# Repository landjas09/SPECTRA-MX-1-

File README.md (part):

# SPECTRA MX-1

*STM32-controlled mixed-signal acquisition and generation board*

SPECTRA MX-1 is a four-layer PCB designed in KiCad for low-frequency analog acquisition and signal generation, with a target operating band of **20 Hz–20 kHz**. An STM32F103 controls an external differential-input ADC and a dual-channel DAC through separate SPI interfaces. The board combines input conditioning, active filtering, reference generation, USB-C connectivity and BNC analog connectors.

**Revision:** A · **Author:** [Akram Landjas](https://github.com/landjas09) ·

*Studio visualization of the Rev A assembly.*

## Contents

- [Project status](#project-status)
- [Hardware specification](#hardware-specification)
- [System architecture](#system-architecture)
- [Analog acquisition path](#analog-acquisition-path)
- [Analog generation path](#analog-generation-path)
- [Nominal filter analysis](#nominal-filter-analysis)
- [Power architecture](#power-architecture)
- [MCU, clocks and pin assignments](#mcu-clocks-and-pin-assignments)
- [External interfaces](#external-interfaces)
- [PCB stackup and mechanics](#pcb-stackup-and-mechanics)
- [BOM and component selection](#bom-and-component-selection)
- [Firmware scope](#firmware-scope)
- [Bring-up and validation](#bring-up-and-validation)
- [Pre-release engineering review](#pre-release-engineering-review)
- [3D models, renders and animation](#3d-models-renders-and-animation)
- [Development roadmap](#development-roadmap)
- [Contributing and technical feedback](#contributing-and-technical-feedback)
- [References](#references)
- [Acknowledgments and licensing](#acknowledgments-and-licensing)

## Project status

This documentation describes the supplied **Rev A PCB snapshot**, saved by KiCad 10.0. Connections, values, component references and stackup data were extracted from MixedSignal_Analyzer_Generator.kicad_pcb. Device characteristics are identified separately from calculated circuit estimates and board measurements.

| Item | Current status |
| --- | --- |
| PCB layout and embedded footprints | Available in the supplied PCB snapshot |
| Board/component 3D export | Available as SPECTRA_MX1.glb |
| Studio renders and animation | Available |
| Main project file, root schematic and child sheets | Included in the repository |
| Custom library sources and library tables | Required for a complete editable project release |
| BOM / purchasing data | Draft; imported metadata and generic components require review |
| Firmware and host software | Not included in the reviewed handoff |
| ERC, DRC and fabrication-release reports | Results not supplied |
| Fabrication, assembly and electrical validation | Pending |
| Measured bandwidth, noise, distortion, ENOB and throughput | Pending |

The 20 Hz–20 kHz band is a **design target**. Converter bit depths are device specifications. The filter plots below are **analytical estimates using the current component values**. A validated input range, output load rating and sustained streaming rate have not yet been established.

## Hardware specification

| Parameter | Rev A implementation / interpretation |
| --- | --- |
| MCU | U200: STM32F103CBTx; manufacturer-part field identifies STM32F103CBT6 |
| MCU resources | Arm Cortex-M3; 128 KB Flash, 20 KB SRAM; device supports a CPU clock up to 72 MHz |
| External clock | Y200: 16 MHz crystal; C208/C209: 10 pF; R201: 0 Ω series link |
| External ADC | U302: ADC141S626CIMM/NOPB; 14-bit SAR, differential input, external reference |
| ADC bus | SPI1; chip select, clock and data-out routed; MCU MOSI not used for this ADC |
| ADC device conversion-rate range | Manufacturer specifies 50–250 kSPS; timing/performance conditions must be checked for the board's nominal 3.3 V supplies |
| ADC voltage reference | U303: REF3033; nominal 3.3 V |
| DAC | U400: DAC7563SDGSR; two 12-bit buffered voltage-output channels |
| DAC bus / controls | SPI2; independent active-low SYNC, LDAC and CLR control |
| Externally routed DAC output | Channel A through the reconstruction filter to J400 |
| DAC channel B | Connected to R402, a 10 kΩ load to GND; no second analog-output connector |
| Op amps | Four MCP6001U devices: U102, U300, U301 and U401 |
| Analog input | J300: single-ended BNC; AC-coupled conditioning and biased converter drive |
| Analog output | J400: BNC; DC-coupled filtered voltage output with 49.9 Ω series resistor |
| Host interface | J201: USB-C receptacle carrying USB 2.0 D+/D− and 5 V VBUS; MCU supports USB full speed |
| Debug | J200: 2 × 5, 1.27 mm header carrying SWD, SWO, reset, GND and 3.3 V reference |
| Primary supply | USB-C VBUS, nominal 5 V |
| Power domains | +5V, +3.3V, +3.3VA, MCU VDDA, buffered VCOM and ADC reference |
| PCB | Four copper layers; current internal zones connect both In1.Cu and In2.Cu to GND |
| Board outline | Approximately 60 × 75 mm, excluding protruding connector bodies |
| Mounting | Four 3.2 mm non-plated M3 mounting holes |
| Modeled finish / thickness | ENIG; approximately 1.57 mm copper/dielectric stack, approximately 1.60 mm including modeled solder mask |
| Design tool | PCB file identifies KiCad 10.0 |

Device limits and specifications above do not establish equivalent board-level performance. See the [manufacturer references](#references) and [validation plan](#bring-up-and-validation).

## System architecture

```mermaid
flowchart TD
    IN["J300: BNC input"] --> FRONT["Protection, coupling and U300 buffer"]
    FRONT --> AAF["Three-pole filter: U301"]
    AAF --> ADC["U302: 14-bit ADC"]
    ADC --> MCU["U200: STM32F103"]
    USB["J201: USB-C host interface"] <--> MCU
    DEBUG["J200: SWD / SWO / reset"] --> MCU
    MCU --> DAC["U400: 12-bit DAC, channel A"]
    DAC --> RECON["Three-pole filter: U401"]
    RECON --> OUT["J400: BNC output"]
```

The input and output processing chains are physically grouped near the BNC connectors. The digital-control and USB circuitry occupy the upper part of the PCB. Separate SPI peripherals allow acquisition and generation to be scheduled independently.

**Rev A bias generation is fixed:** VCOM is produced by a resistor divider and an op-amp buffer. DAC channel B is not connected to the bias generator in this snapshot.

## Analog acquisition path

### Input connector and protection

J300's center contact connects to /ADC/IN; its shield contacts connect to GND. D300, labeled CDSOD323-T03C, is placed between the input net and GND.

R300 = 1 kΩ and C300 = 150 pF form the first input RF-filtering network. R301 = 2.2 MΩ provides a return path from /ADC/IN_RF to GND.

Ignoring the following coupling/bias network and source impedance, the simple R300/C300 pole is approximately **1.06 MHz**. Its role is upstream high-frequency filtering; the following active filter sets the useful low-frequency response.

### AC coupling, bias and first buffer

C301 = 100 nF connects /ADC/IN_RF to /ADC/IN_BUFF. R302 = 2.2 MΩ biases /ADC/IN_BUFF to VCOM. U300 is an MCP6001U configured as a unity-gain buffer.

For a low-impedance source, the dominant coupling estimate is:

$$
f_{\mathrm{HP}} \approx \frac{1}{2\pi R_{302}C_{301}} \approx 0.72\ \mathrm{Hz}.
$$

This estimate depends on the source and the other return paths. **20 Hz is the lower edge of the stated target band, not the calculated −3 dB frequency of C301/R302.** The high-value bias resistance also makes leakage, contamination and startup settling relevant during assembly and validation.

### Active anti-alias filter

The signal at /ADC/IN_BUFF_OUT passes through a three-pole unity-gain RC/active network using U301. The topology combines the initial RC section with a buffered Sallen–Key section.

| Function | Components |
| --- | --- |
| First series resistor / shunt capacitor | R303 = 6.8 kΩ; C303 = 1 nF |
| Following series resistors | R304 = 22 kΩ; R305 = 12 kΩ |
| Feedback capacitor to the buffer output | C305 = 1 nF |
| Final input shunt capacitor | C304 = 150 pF |
| Unity-gain buffer | U301, MCP6001U |

The resulting nominal response is discussed in [Nominal filter analysis](#nominal-filter-analysis). Actual response depends on op-amp behavior, component tolerances and loading.

### Converter input network

U301 drives /ADC/ADC_IN+ through R306 = 1 kΩ. The ADC negative input is biased from VCOM through R307 = 1 kΩ. C307 = 150 pF connects the two ADC input nets.

This produces a nominal differential RC pole around **531 kHz** when approximated using R306 + R307. The actual SAR sampling network adds switched-capacitor loading, so acquisition settling must also be checked.

The external BNC signal is single-ended. The ADC measures the conditioned positive input relative to the biased negative input.

### ADC reference and supplies

- U302 VA, pin 10, connects to +3.3VA.
- U302 VIO, pin 9, connects to +3.3V.
- U303 REF3033 receives +5V through R308 = 49.9 Ω.
- C309 = 10 µF filters /ADC/ADC_VREF_VIN.
- U303's output connects to /ADC/ADC_Vref and U302 pin 1.
- C310 = 10 µF and C311 = 100 nF decouple the ADC reference.

The ideal R308/C309 supply-filter pole is approximately **319 Hz**. It is an input-supply filter for the reference, not a series filter between the reference output and ADC pin.

### Code interpretation and input range

The ADC's serial result is a **14-bit signed two's-complement value**. After extracting and sign-extending the conversion bits correctly, its ideal differential-voltage relationship is:

$$
V_{\mathrm{IN+}}-V_{\mathrm{IN-}}
\approx D_{\mathrm{signed}}\frac{2V_{\mathrm{REF}}}{2^{14}}.
$$

At nominal VREF = 3.3 V, the ideal differential code step is approximately **0.403 mV**.

The selected reference and input topology require engineering review. TI's full-range single-ended guidance uses VREF no greater than VA/2. Rev A selects a nominal 3.3 V reference while driving the ADC from a nominal 3.3 V analog supply and holding the negative input near 1.65 V. Reference tolerance, valid common-mode range, available signal swing and code utilization must therefore be resolved before publishing an external-input amplitude rating.

## Analog generation path

### DAC and digital control

U400 is a DAC7563 dual-channel, 12-bit voltage-output DAC. SPI2 carries commands to its DIN pin, with separate GPIO control for SYNC, LDAC and CLR.

The DAC accepts a **24-bit serial command frame**. Firmware must follow the command/address/data arrangement and timing in the DAC7563 datasheet; the register width is distinct from its 12-bit conversion resolution.

In Rev A:

- Channel A, /DAC/DAC_OUT_A, drives the output-filter chain.
- Channel B, /DAC/DAC_OUT_B, is connected to R402 = 10 kΩ to GND.
- AVDD connects to +3.3V.
- C400 = 10 µF and C401 = 100 nF decouple the supply.
- C402 = 1 µF connects the reference pin to GND.

### Reference and gain configuration

The internal 2.5 V reference is available by command and is disabled at power-up. Enabling it selects a gain configuration that must be handled explicitly.

For this nominal 3.3 V supply, **gain = 1 with the internal 2.5 V reference is the proposed initial configuration**. A 5 V full-scale request from gain = 2 exceeds the supply headroom. This is a firmware requirement to validate, not an implemented configuration reported by this repository.

For gain = 1:

$$
V_{\mathrm{DAC,A}} \approx 2.5\ \mathrm{V}\frac{D}{4096},
\qquad 0\le D\le4095.
$$

The ideal code step is approximately 0.610 mV. Codes 0, 2048 and 4095 nominally request 0 V, 1.25 V and 2.4994 V before output errors and loading. These are calculation values for bring-up, not measured output specifications.

### Reconstruction filter and BNC output

| Function | Components |
| --- | --- |
| First series resistor / shunt capacitor | R401 = 6.8 kΩ; C403 = 1 nF |
| Following series resistors | R403 = 22 kΩ; R404 = 12 kΩ |
| Feedback capacitor to the buffer output | C406 = 1 nF |
| Final input shunt capacitor | C404 = 150 pF |
| Unity-gain output buffer | U401, MCP6001U |
| BNC series resistor | R405 = 49.9 Ω |
| Output protection device | D400, CDSOD323-T03C |

The filter values match the ADC anti-alias network. U401's output drives J400 through R405. There is **no series output AC-coupling capacitor** in the reviewed path, so the output carries its DC level as well as the generated waveform.

R405 contributes approximately 50 Ω of series resistance. A 50 Ω BNC connector designation does not establish a validated 50 Ω load-drive capability. Initial characterization should use a high-impedance measurement input; output-current capability, loaded swing and cable-capacitance stability remain to be measured.

## Nominal filter analysis

Both active low-pass stages use the same resistor/capacitor values. A small-signal model with an ideal unity-gain buffer gives:

$$
H_{\mathrm{LP}}(s)=
\frac{1}{
1+(12.92\times10^{-6})s+
(8.652\times10^{-11})s^2+
(2.6928\times10^{-16})s^3
},
\qquad s=j2\pi f.
$$

| Frequency / metric | Ideal response of one low-pass stage |
| --- | --- |
| DC gain | 1 V/V |
| 1 kHz | Approximately +0.001 dB |
| 10 kHz | Approximately +0.050 dB |
| 20 kHz | Approximately −1.21 dB |
| −3 dB frequency | Approximately 24.05 kHz |
| 40 kHz | Approximately −13.22 dB |
| 50 kHz | Approximately −18.76 dB |
| 100 kHz | Approximately −36.57 dB |
| High-frequency asymptotic slope | −60 dB/decade |

**Model scope:** this is the common three-pole low-pass network only. It excludes finite op-amp gain/bandwidth, ADC sampling kickback, reference noise, source/load impedance, component tolerances, coupling/protection networks and PCB parasitics. End-to-end DAC-to-ADC loopback passes through both low-pass stages.

The [analysis script](docs/analysis/nominal_filter.py) and [numerical results](docs/analysis/nominal_filter_results.json) accompany this README.

To regenerate the analytical figure and results:

```bash
python -m pip install numpy scipy matplotlib
python docs/analysis/nominal_filter.py
```

For a 20 kHz signal band, the sample rate must exceed 40 kSPS and provide practical anti-aliasing margin. The existing filter's attenuation at the chosen Nyquist frequency must be evaluated against the required alias rejection. No ADC sample rate, DAC update rate or spectral-performance result is claimed as firmware-validated yet.

## Power architecture

```mermaid
flowchart TD
    VBUS["USB-C VBUS: nominal 5 V"] --> ENTRY["L100 and entry capacitors"]
    ENTRY --> FIVE["+5V"]
    FIVE --> BUCK["U100: buck to +3.3V"]
    BUCK --> DIGITAL["MCU, DAC and ADC digital supply"]
    FIVE --> AIN["R100 / C102 input filter"]
    AIN --> LDO["U101: +3.3VA analog rail"]
    LDO --> ANALOG["Op amps and ADC analog supply"]
    LDO --> BIAS["Divider and U102: VCOM"]
    FIVE --> RIN["R308 / C309 input filter"]
    RIN --> REF["U303: ADC reference"]
```

### USB entry and digital rail

L100 is labeled **100 nH** in the inductor symbol. C101 = 1 µF is connected from VBUS to GND, and C100 = 1 µF is connected from +5V to GND.

U100 TLV62569DBVR generates the digital rail. Its enable and input pins connect to +5V. L101 is labeled MWSA0603S-150MT; imported component metadata identifies 15 µH. C104 and C105 are 22 µF input/output capacitors.

With R101 = 100 kΩ, R102 = 22 kΩ and the regulator's nominal 0.6 V feedback reference:

$$
V_{\mathrm{OUT,ideal}}\approx0.6(1+100/22)\approx3.327\ \mathrm{V}.
$$

The rail is named +3.3V. Its assembled regulation, ripple, startup and load response must be measured. C106 is a feed-forward capacitor footprint labeled DNP.

The regulator's component rating does not establish a 2 A USB-powered board rating. Available current depends on the USB source, entry network, inductor, thermal behavior and the final power budget.

### Analog supply

R100 = 10 Ω and C102 = 22 µF filter the +5V supply before U101, labeled HT7533-1. U101's output is +3.3VA, with C103 = 22 µF on that rail.

The ideal input RC pole is approximately **723 Hz**. R100 also creates a load-dependent DC drop, so LDO dropout and analog current must be checked together.

The imported U101 manufacturer field identifies UMW. Confirm the exact supplier part, current rating, pinout and stability requirements when completing the BOM rather than assuming every similarly named regulator has identical specifications.

### VCOM generation

R105 = 1 kΩ to +3.3VA and R104 = 1 kΩ to GND form a nominal half-supply divider. C107 = 22 µF filters the divider node, /Power/VREF. U102 MCP6001U buffers it as VCOM.

VCOM is nominally **1.65 V** when +3.3VA is 3.3 V. The divider's 500 Ω Thevenin resistance and C107 give an ideal pole near **14.5 Hz**. The buffer supplies the bias node without asking the divider to drive the ADC input network directly.

### MCU analog supply

L201 = 10 nH connects +3.3V to the MCU's VDDA net. C205 = 10 nF and C206 = 1 µF decouple VDDA; U200 VSSA connects to GND.

**VDDA and +3.3VA are distinct nets:** VDDA supplies the MCU's analog domain, while +3.3VA supplies the external analog circuitry and ADC VA.

| Net | Source / nominal value | Main loads |
| --- | --- | --- |
| VBUS | USB-C, nominal 5 V | Entry filter and USB protection reference |
| +5V | VBUS after L100 | Buck, analog-supply filter and ADC-reference supply filter |
| +3.3V | U100 buck, nominal 3.3 V | MCU VDD/VBAT, DAC AVDD, ADC VIO, LED and debug reference |
| +3.3VA | U101 linear regulator, nominal 3.3 V | U102/U300/U301/U401 and ADC VA |
| VDDA | +3.3V through L201 | MCU analog supply |
| VCOM | Divider followed by U102, nominal 1.65 V | Input bias and ADC negative-input network |
| /ADC/ADC_Vref | U303, nominal 3.3 V | External ADC reference |
| /DAC/DAC_VREF | U400 reference pin with C402 | DAC reference node; internal reference needs firmware configuration |

## MCU, clocks and pin assignments

### MCU and clock source

U200 is an STM32F103CBT6 in LQFP48. Its VDD and VBAT pins connect to +3.3V; its VSS and VSSA pins connect to GND.

Y200 is labeled 16 MHz. C208 and C209 are 10 pF crystal-load capacitors. R201 is a 0 Ω series link between HSE_OUT and the crystal-side /Mcu/XTAL_IN net. The exact crystal orderable part and load-capacitance requirement remain BOM decisions.

A **proposed** clock configuration for firmware bring-up is HSE = 16 MHz, HSE divided by two into the PLL, PLL ×9 for 72 MHz, and the appropriate USB divider for 48 MHz. This configuration is not present as validated firmware in the supplied files. Firmware must account for APB limits and the timer/peripheral clock tree.

### Interface pin map

These assignments come from the actual U200 pad nets. Package pins refer to the reviewed LQFP48 footprint.

| Function | MCU port | Package pin | PCB net / connection |
| --- | --- | ---: | --- |
| ADC chip select | PA4 | 14 | /SPI1_NSS → U302 NCS |
| ADC serial clock | PA5 | 15 | /SPI1_SCK → R309, 0 Ω → ADC SCLK |
| ADC serial data | PA6 | 16 | /SPI1_MISO ← U302 DOUT |
| DAC frame select | PB12 | 25 | /SPI2_NSS → U400 NSYNC |
| DAC serial clock | PB13 | 26 | /SPI2_SCK → R400, 0 Ω → DAC SCLK |
| DAC serial data | PB15 | 28 | /SPI2_MOSI → U400 DIN |
| DAC clear | PB2 | 20 | /DAC_NCLR → U400 NCLR |
| DAC update latch | PB10 | 21 | /DAC_NLDAC → U400 NLDAC |
| USB D− | PA11 | 32 | /Mcu/USB_D- |
| USB D+ | PA12 | 33 | /Mcu/USB_D+ |
| SWD data | PA13 | 34 | /Mcu/SWDIO → R210 → J200 |
| SWD clock | PA14 | 37 | /Mcu/SWCLK → R211 → J200 |
| Trace output | PB3 | 39 | /Mcu/SWO → R212 → J200 |
| Reset | NRST | 7 | /Mcu/NRST → R213 → J200 |
| Crystal input | PD0 | 5 | /Mcu/HSE_IN |
| Crystal output | PD1 | 6 | /Mcu/HSE_OUT → R201 → crystal |
| Boot selection | BOOT0 | 44 | /Mcu/BOOT; R200 = 10 kΩ to GND |
| RGB red cathode drive | PB8 | 45 | /Mcu/TIM4-CH1 → R207 → red |
| RGB green cathode drive | PB6 | 42 | /Mcu/TIM4-CH2 → R208 → green |
| RGB blue cathode drive | PB7 | 43 | /Mcu/TIM4-CH3 → R209 → blue |

PA7/SPI1 MOSI and PB14/SPI2 MISO are unconnected in this layout. PB2 also has the STM32 boot-selection role associated with BOOT1; boot-mode changes must account for its DAC-clear connection.

### Indicator mapping

D100 is the green digital-power indicator, with R103 = 1 kΩ to GND.

D206 is a common-anode RGB LED powered from +3.3V. R207/R208/R209 are 1 kΩ series resistors; the MCU sinks LED current.

| LED color | Physical MCU pin | Default TIM4 channel | Current PCB net label |
| --- | --- | --- | --- |
| Red | PB8 | TIM4_CH3 | /Mcu/TIM4-CH1 |
| Green | PB6 | TIM4_CH1 | /Mcu/TIM4-CH2 |
| Blue | PB7 | TIM4_CH2 | /Mcu/TIM4-CH3 |

The existing TIM4 net labels differ from the default STM32 alternate-function mapping. Firmware configuration should follow the **physical pins and the STM32 pin-multiplexing table**. Net-label cleanup belongs in the pre-release review.

## External interfaces

### USB-C — J201

J201 is a 16-contact USB 2.0 Type-C receptacle using the GCT USB4105 footprint family.

| Connection | Rev A implementation |
| --- | --- |
| VBUS contacts | Joined to VBUS; nominal 5 V bus power |
| GND contacts | Joined to GND |
| D+ / D− contacts on both orientations | Joined by signal and routed to the USB protection/filter chain |
| CC1 | R206 = 5.1 kΩ to GND |
| CC2 | R205 = 5.1 kΩ to GND |
| SBU1/SBU2 | Unconnected |
| Shield pads | Marked unconnected in the reviewed PCB |

The data path is J201 → U201 USBLC6-2SC6 protection → L200 CMF3216F-900-2P-T common-mode choke → PA11/PA12. R204 = 1.5 kΩ connects USB D+ to +3.3V for the full-speed pull-up.

The CC pull-downs implement the board's sink-side connection. No USB Power Delivery controller is present. Higher-voltage PD modes are outside this hardware configuration.

USB descriptors, device class, enumeration and data-transfer performance depend on firmware that has not yet been supplied. Shield/chassis termination also requires an explicit final decision.

### SWD / trace / reset — J200

J200 is an **unshrouded 2 × 5 pin header at 1.27 mm pitch**. Identify pin 1 from the footprint pad/silkscreen before attaching a cable.

| Pin | Signal | Board connection |
| ---: | --- | --- |
| 1 | Target voltage reference | +3.3V |
| 2 | SWDIO | PA13 through R210 = 49.9 Ω |
| 3 | GND | GND |
| 4 | SWCLK | PA14 through R211 = 49.9 Ω |
| 5 | GND | GND |
| 6 | SWO | PB3 through R212 = 49.9 Ω |
| 7 | Unconnected | No electrical connection; the header has no blocking key |
| 8 | Unconnected | No TDI connection |
| 9 | GND | GND |
| 10 | NRST | MCU reset through R213 = 49.9 Ω |

Pin 1 presents the target's logic-voltage reference; external target powering through this pin is not established as a supported power method. D200/D201/D203/D204 protect the connector-side SWDIO, SWCLK, SWO and reset nets; D205 is connected between +3.3V and GND.

The connector-side SWO net is spelled /Mcu/SW0_CONN in the source. It connects to the MCU's SWO signal despite the zero in that label.

### BNC connectors — J300 and J400

Both connectors use the Amphenol B6252HB-NPP3G-50 horizontal BNC footprint family. Confirm the exact connector order code, mechanical dimensions and mating clearance when finalizing the BOM.

| Connector | Center contact | Shield | Function |
| --- | --- | --- | --- |
| J300, IN | /ADC/IN | GND | Single-ended, AC-coupled analog input |
| J400, OUT | /DAC/OUT | GND | Filtered, DC-coupled DAC channel-A output |

The two ports share the board's common ground. Output load capability and external-input amplitude limits remain validation items.

## PCB stackup and mechanics

### Current copper/reference arrangement

The source contains routed segments on F.Cu and B.Cu, with a GND zone assigned to **both internal layers**.

| Layer | Copper thickness | Current use |
| --- | ---: | --- |
| L1 — F.Cu | 35 µm | Components, signal routing and local power/GND pours |
| L2 — In1.Cu | 17.5 µm | GND zone |
| L3 — In2.Cu | 17.5 µm | GND zone |
| L4 — B.Cu | 35 µm | Signal routing |

The exported reference arrangement is therefore **signal / ground / ground / signal**. Layer classifications in KiCad do not override the actual zone-net assignments.

| Dielectric interval | File type | Modeled thickness | Material parameters |
| --- | --- | ---: | --- |
| F.Cu → In1.Cu | Core | 0.100 mm | FR4; εr = 4.5, loss tangent = 0.02 |
| In1.Cu → In2.Cu | Core | 1.265 mm | FR4; εr = 4.5, loss tangent = 0.02 |
| In2.Cu → B.Cu | Prepreg | 0.100 mm | FR4; εr = 4.5, loss tangent = 0.02 |

The modeled bare copper/dielectric stack sums to **1.570 mm**. The two 12.7 µm solder-mask layers bring the model to approximately **1.595 mm**. Final laminate construction, tolerances and impedance must be agreed with the fabricator.

### Layout snapshot

- Board outline: approximately 60 × 75 mm with rounded corners.
- Four non-plated 3.2 mm mounting holes, M01–M04.
- 116 total footprint records: 110 electrical component positions, four mounting holes and two artwork footprints.
- 662 track segments: 580 on F.Cu and 82 on B.Cu.
- 383 vias in the snapshot, including 346 assigned to GND.
- Stored track widths include 0.229, 0.29337, 0.300 and 0.500 mm.
- ENIG is the finish recorded in the board stackup.
- Smallest ordinary passive footprints are 0402 imperial / 1005 metric.

These counts describe the file and do not certify routing completeness, return-path quality or DRC clearance. Verify filled copper around vias, connector pads and transitions; stored width values alone do not establish controlled impedance.

### Placement and reference strategy

The layout groups the sensitive input, reference and conversion networks near U302 and keeps the generation filter near J400. U100's switching circuit and the digital/USB area occupy separate regions from the main BNC signal paths.

Review priorities are the buck input/switching/output loops, decoupling loops, ADC-reference charging path, crystal loop and continuous references beneath USB/SPI routes. Ground stitching should support transitions and field containment; its effectiveness depends on placement and connectivity.

## BOM and component selection

**BOM status: draft.** Current nominal values and imported ordering metadata are documented; production purchasing fields and assembly decisions are not complete.

The [extracted board inventory](docs/board-inventory.md) lists all 110 electrical positions with footprint identifiers and available manufacturer/part fields.

| References | Source value / family | Role |
| --- | --- | --- |
| U100 | TLV62569DBVR | Digital-rail buck regulator |
| U101 | HT7533-1 | Analog-rail linear regulator; imported supplier metadata identifies UMW |
| U102 | MCP6001U | VCOM buffer |
| U200 | STM32F103CBT6 manufacturer-part field | MCU |
| U201 | USBLC6-2SC6 | USB data-line protection |
| U300 | MCP6001U | Input buffer |
| U301 | MCP6001U | Anti-alias filter buffer |
| U302 | ADC141S626CIMM/NOPB | External ADC |
| U303 | REF3033 | ADC reference |
| U400 | DAC7563SDGSR | DAC |
| U401 | MCP6001U | Output-filter buffer |
| L100 / L201 | 100 nH / 10 nH labels | Supply-filter inductors |
| L101 | MWSA0603S-150MT; imported 15 µH description | Buck output inductor |
| L200 | CMF3216F-900-2P-T | USB common-mode choke |
| D200/D201/D203/D204/D205/D300/D400 | CDSOD323-T03C | Debug, supply and analog-port protection |
| Y200 | 16 MHz | HSE crystal |
| J200 | 2 × 5, 1.27 mm header | SWD interface |
| J201 | USB-C, USB4105 footprint family | USB / power entry |
| J300/J400 | B6252HB-NPP3G-50 footprint family | BNC ports |

Before purchasing, normalize imported field names such as Manufacturer, MF, MANUFACTURER, MP and Manufacturer Part Number. Imported availability/price text is not a current procurement check.

Finalize exact orderable codes, package/pin variants, voltage/power ratings, resistor tolerances, capacitor dielectric/tolerance/DC-bias behavior, inductor saturation/DCR and crystal load requirements. Confirm MCP6001U's pin arrangement and the converters' 10-pin DGS package land patterns.

**C106 is intentionally labeled DNP in its value field.** Its source PCB attributes do not include the DNP flag. Align schematic/PCB population flags and exported BOM/position data before assembly.

### Opening the design

1. Use KiCad 10.0 or a compatible newer version for this PCB file.
2. For the complete project, open the main .kicad_pro file after it and the complete schematic hierarchy are published.
3. For the reviewed layout snapshot, open MixedSignal_Analyzer_Generator.kicad_pcb directly in PCB Editor.
4. Install/relink custom libraries using project-relative paths and the supplied library tables.
5. Refill copper zones, check the stackup and run the release checks against the same source revision.

The PCB embeds its placed footprints, so the layout can be inspected without every original library. Editing symbols, updating footprints or synchronizing from a schematic requires the complete library/project sources.

Custom identifiers present in the snapshot include Footprints:SOIC-10-adc141s626, Footprints:TLV-SOT95P280X145-5N, Footprints:STM-LQFP-48_7x7mm_P0.5mm, Footprints:LDO-SOT89, Footprints:CMC-1206 and Footprints:INDM7066X300N. The converter footprint's name should not substitute for checking the actual VSSOP/MSOP package dimensions.

## Firmware scope

Firmware is a **planned implementation** in the reviewed handoff. No build command, binary, USB protocol or runtime result is supplied here.

| Area | Implementation requirements |
| --- | --- |
| Clock initialization | Match the 16 MHz HSE, CPU/APB limits and required USB clock |
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
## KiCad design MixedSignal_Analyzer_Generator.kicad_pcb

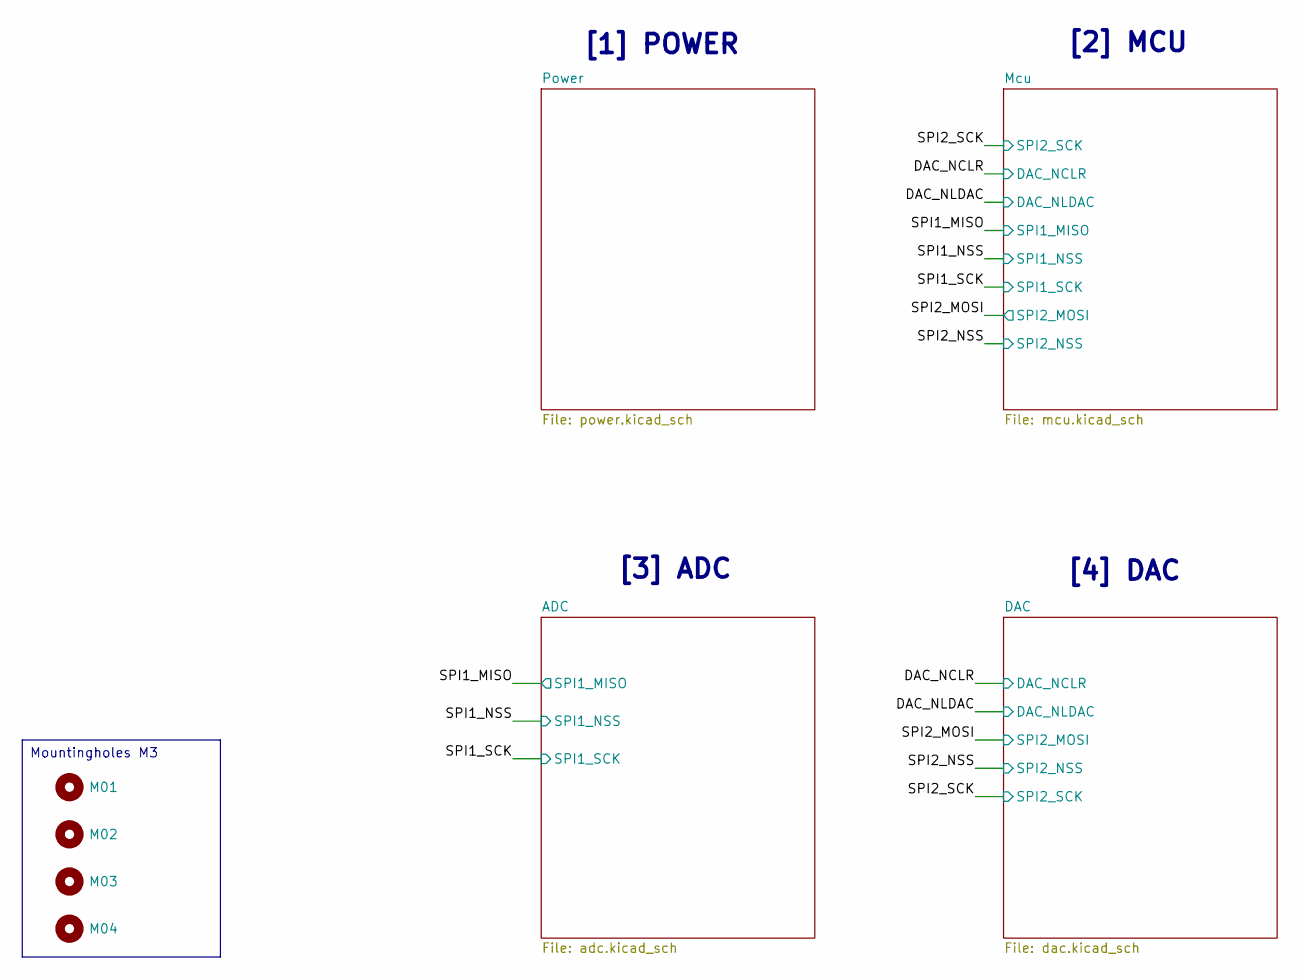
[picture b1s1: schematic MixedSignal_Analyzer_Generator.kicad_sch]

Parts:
M01, M02, M03, M04: MountingHole; MountingHole_3.2mm_M3

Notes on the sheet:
[3] ADC
[2] MCU
[4] DAC
[1] POWER
Mountingholes M3

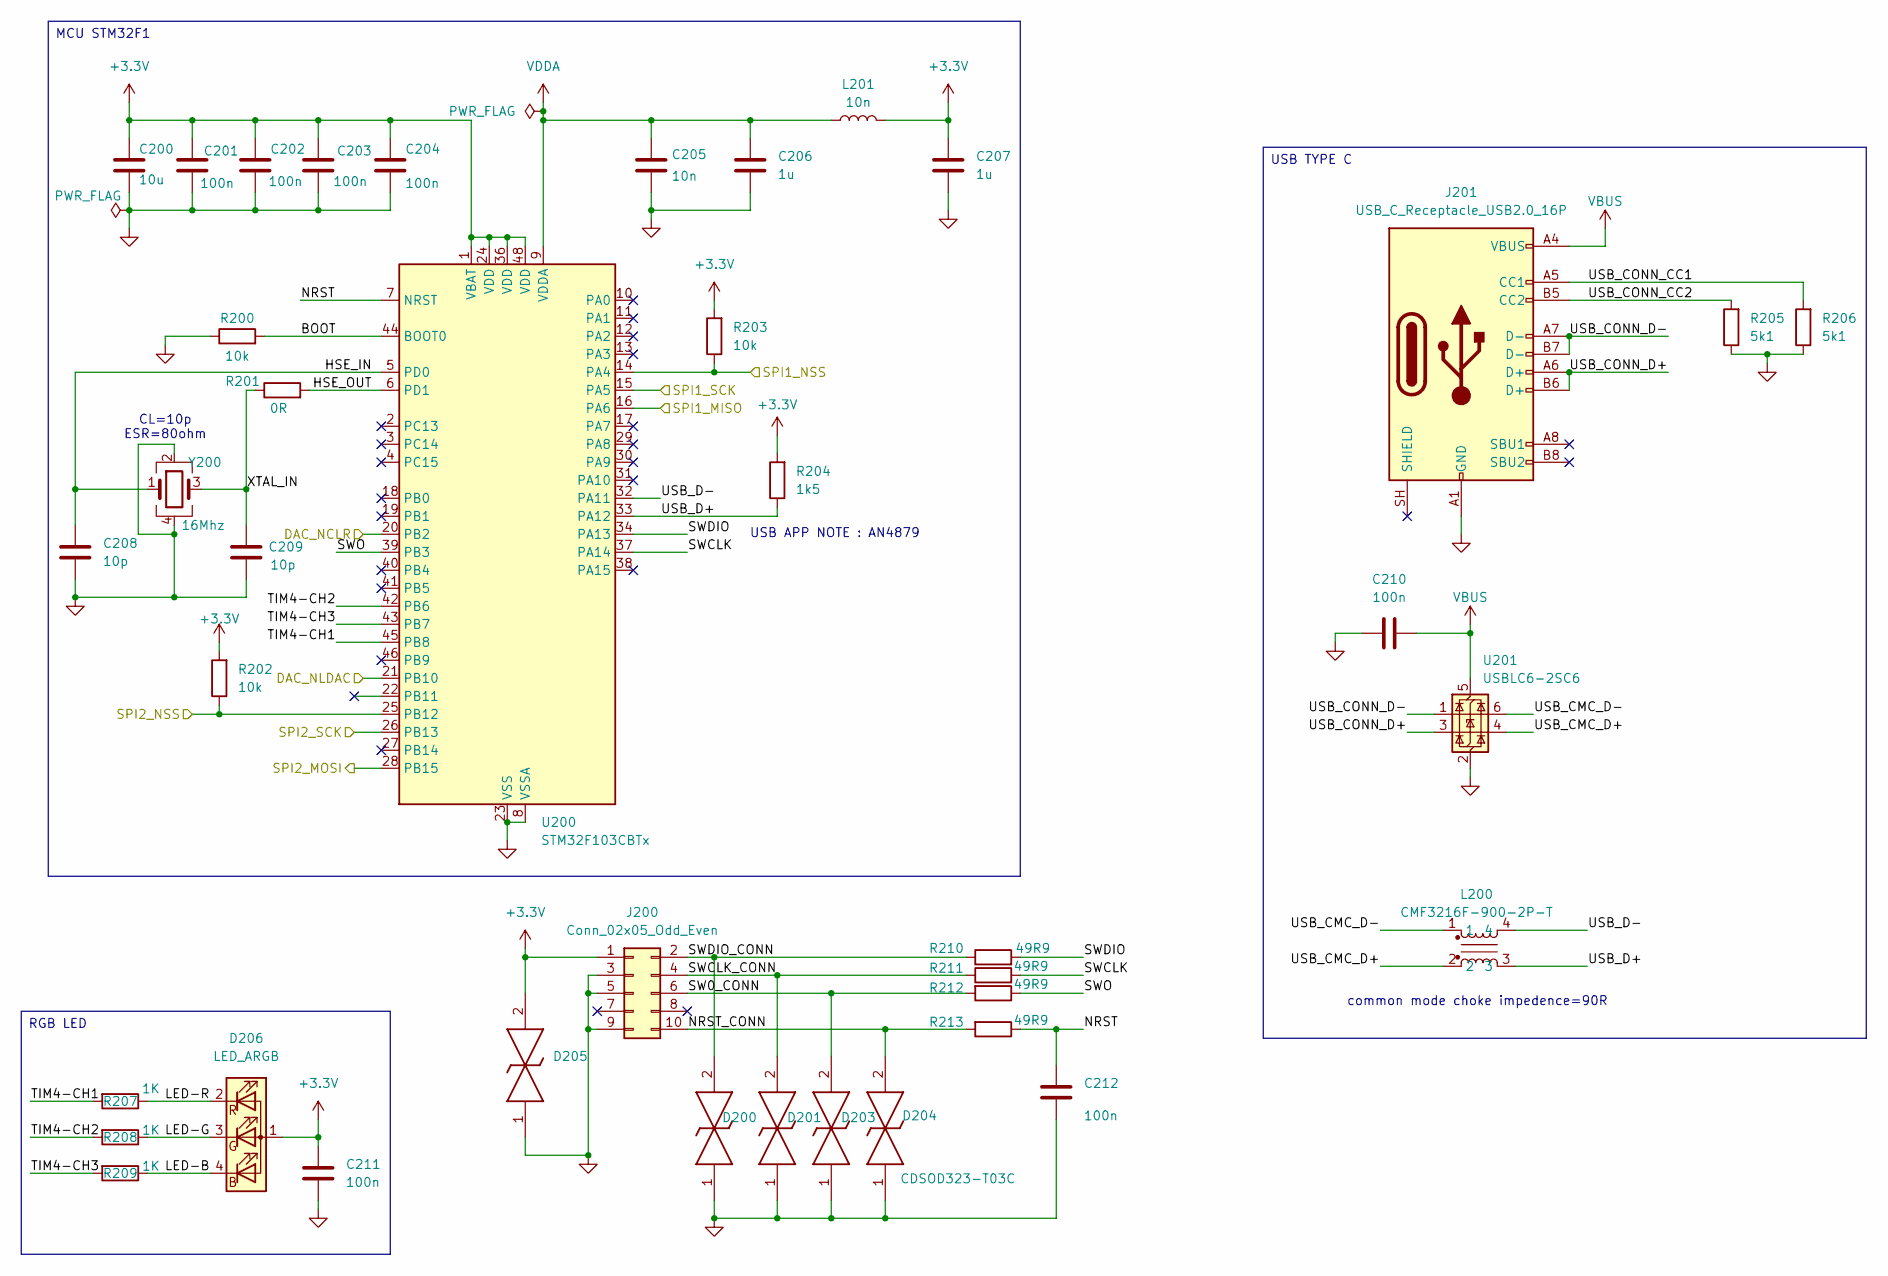
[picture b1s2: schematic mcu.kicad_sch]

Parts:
C200: 10u; C_0603_1608Metric
C201, C202, C203, C204, C210, C211, C212: 100n; C_0402_1005Metric
C205: 10n; C_0402_1005Metric
C206, C207: 1u; C_0603_1608Metric
C208, C209: 10p; C_0402_1005Metric
D200, D201, D203, D204, D205: CDSOD323-T03C; SOD2513X114N; Mouser Part Number 652-CDSOD323-T03C
D206: LED_ARGB; LED_RGB_Wuerth-PLCC4_3.2x2.8mm_150141M173100
J200: Conn_02x05_Odd_Even; PinHeader_2x05_P1.27mm_Vertical
J201: USB_C_Receptacle_USB2.0_16P; USB_C_Receptacle_GCT_USB4105-xx-A_16P_TopMnt_Horizontal
L200: CMF3216F-900-2P-T; CMC-1206
L201: 10n; L_0402_1005Metric
R200, R202, R203: 10k; R_0402_1005Metric
R201: 0R; R_0402_1005Metric
R204: 1k5; R_0402_1005Metric
R205, R206: 5k1; R_0402_1005Metric
R207, R208, R209: 1K; R_0402_1005Metric
R210, R211, R212, R213: 49R9; R_0402_1005Metric
U200: STM32F103CBTx; STM-LQFP-48_7x7mm_P0.5mm
U201: USBLC6-2SC6; SOT-23-6
Y200: 16Mhz; Crystal_SMD_3225-4Pin_3.2x2.5mm

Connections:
+3.3V: C200.1, C201.1, C202.1, C203.1, C204.1, C207.1, C211.1, D205.2, D206.1 (A), J200.1, L201.2, R202.2, R203.2, R204.2, U200.1 (VBAT), U200.24 (VDD), U200.36 (VDD), U200.48 (VDD); also elsewhere on the board
/DAC_NCLR: U200.20 (PB2); also elsewhere on the board
/DAC_NLDAC: U200.21 (PB10); also elsewhere on the board
/Mcu/BOOT: R200.2, U200.44 (BOOT0)
/Mcu/HSE_IN: C208.1, U200.5 (PD0), Y200.1
/Mcu/HSE_OUT: R201.2, U200.6 (PD1)
/Mcu/LED-B: D206.4 (BK), R209.1
/Mcu/LED-G: D206.3 (GK), R208.1
/Mcu/LED-R: D206.2 (RK), R207.1
/Mcu/NRST: C212.1, R213.1, U200.7 (NRST)
/Mcu/NRST_CONN: D204.2, J200.10, R213.2
/Mcu/SW0_CONN: D203.2, J200.6, R212.2
/Mcu/SWCLK: R211.2, U200.37 (PA14)
/Mcu/SWCLK_CONN: D201.2, J200.4, R211.1
/Mcu/SWDIO: R210.2, U200.34 (PA13)
/Mcu/SWDIO_CONN: D200.2, J200.2, R210.1
/Mcu/SWO: R212.1, U200.39 (PB3)
/Mcu/TIM4-CH1: R207.2, U200.45 (PB8)
/Mcu/TIM4-CH2: R208.2, U200.42 (PB6)
/Mcu/TIM4-CH3: R209.2, U200.43 (PB7)
/Mcu/USB_CMC_D+: L200.2, U201.4 (I/O2)
/Mcu/USB_CMC_D-: L200.1, U201.6 (I/O1)
/Mcu/USB_CONN_CC1: J201.A5 (CC1), R206.2
/Mcu/USB_CONN_CC2: J201.B5 (CC2), R205.2
/Mcu/USB_CONN_D+: J201.A6 (D+), J201.B6 (D+), U201.3 (I/O2)
/Mcu/USB_CONN_D-: J201.A7 (D-), J201.B7 (D-), U201.1 (I/O1)
/Mcu/USB_D+: L200.3, R204.1, U200.33 (PA12)
/Mcu/USB_D-: L200.4, U200.32 (PA11)
/Mcu/XTAL_IN: C209.1, R201.1, Y200.3
/SPI1_MISO: U200.16 (PA6); also elsewhere on the board
/SPI1_NSS: R203.1, U200.14 (PA4); also elsewhere on the board
/SPI1_SCK: U200.15 (PA5); also elsewhere on the board
/SPI2_MOSI: U200.28 (PB15); also elsewhere on the board
/SPI2_NSS: R202.1, U200.25 (PB12); also elsewhere on the board
/SPI2_SCK: U200.26 (PB13); also elsewhere on the board
GND: C200.2, C201.2, C202.2, C203.2, C204.2, C205.2, C206.2, C207.2, C208.2, C209.2, C210.2, C211.2, C212.2, D200.1, D201.1, D203.1, D204.1, D205.1, J200.3, J200.5, J200.9, J201.A1 (GND), J201.A12 (GND), J201.B1 (GND), J201.B12 (GND), R200.1, R205.1, R206.1, U200.8 (VSSA), U200.23 (VSS), U200.35 (VSS), U200.47 (VSS), U201.2 (GND), Y200.2 (G), Y200.4 (G); also elsewhere on the board
VBUS: C210.1, J201.A4 (VBUS), J201.A9 (VBUS), J201.B4 (VBUS), J201.B9 (VBUS), U201.5 (VBUS); also elsewhere on the board
VDDA: C205.1, C206.1, L201.1, U200.9 (VDDA)

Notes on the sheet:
USB APP NOTE : AN4879
common mode choke impedence=90R
CL=10p ESR=80ohm
MCU STM32F1
RGB LED
USB TYPE C

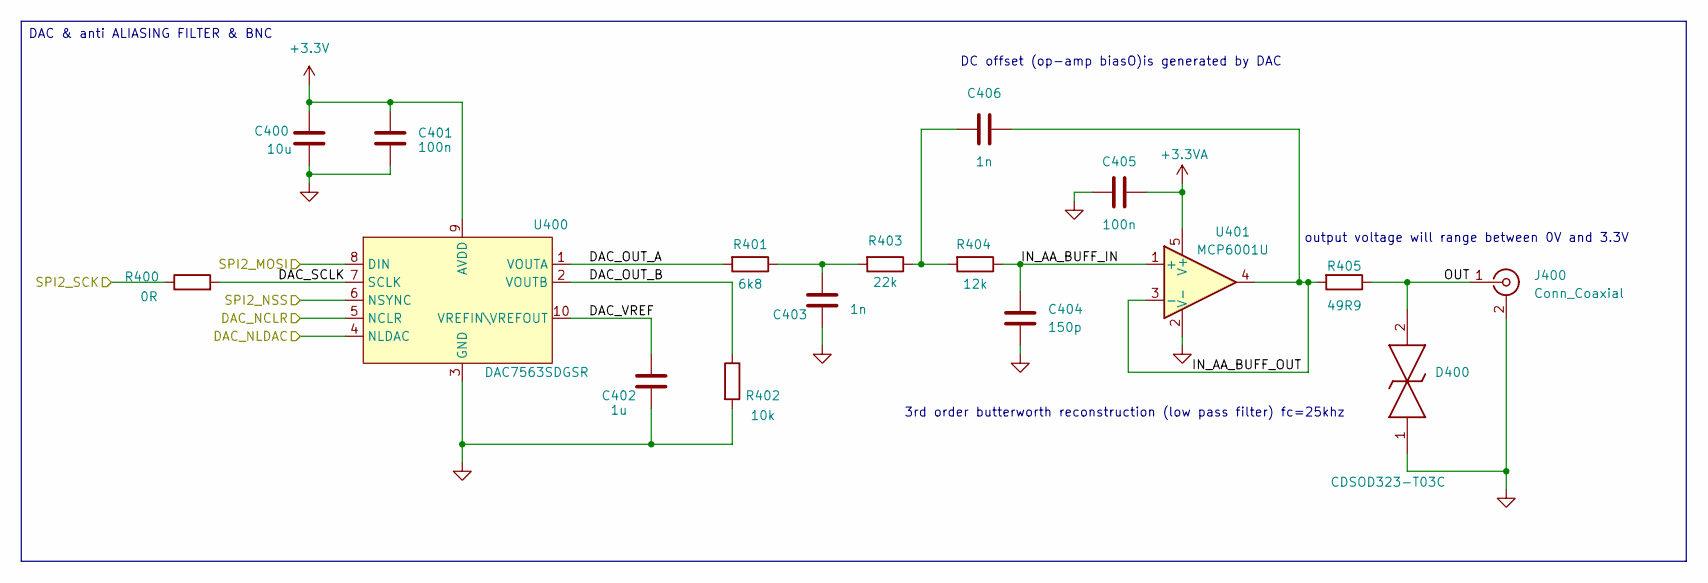
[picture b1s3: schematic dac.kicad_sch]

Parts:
C400: 10u; C_0603_1608Metric
C401, C405: 100n; C_0402_1005Metric
C402: 1u; C_0603_1608Metric
C403, C406: 1n; C_0402_1005Metric
C404: 150p; C_0402_1005Metric
D400: CDSOD323-T03C; SOD2513X114N; Mouser Part Number 652-CDSOD323-T03C
J400: Conn_Coaxial; BNC_Amphenol_B6252HB-NPP3G-50_Horizontal
R400: 0R; R_0402_1005Metric
R401: 6k8; R_0402_1005Metric
R402: 10k; R_0402_1005Metric
R403: 22k; R_0402_1005Metric
R404: 12k; R_0402_1005Metric
R405: 49R9; R_0402_1005Metric
U400: DAC7563SDGSR; SOIC-10-adc141s626
U401: MCP6001U; SOT-23-5

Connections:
+3.3V: C400.1, C401.1, U400.9 (AVDD); also elsewhere on the board
+3.3VA: C405.2, U401.5 (V+); also elsewhere on the board
/DAC/DAC_OUT_A: R401.2, U400.1 (VOUTA)
/DAC/DAC_OUT_B: R402.1, U400.2 (VOUTB)
/DAC/DAC_SCLK: R400.2, U400.7 (SCLK)
/DAC/DAC_VREF: C402.1, U400.10 (VREFIN\VREFOUT)
/DAC/IN_AA_BUFF_IN: C404.1, R404.1, U401.1 (+)
/DAC/IN_AA_BUFF_OUT: C406.2, R405.2, U401.3 (-), U401.4
/DAC/OUT: D400.2, J400.1 (In), R405.1
/DAC_NCLR: U400.5 (NCLR); also elsewhere on the board
/DAC_NLDAC: U400.4 (NLDAC); also elsewhere on the board
/SPI2_MOSI: U400.8 (DIN); also elsewhere on the board
/SPI2_NSS: U400.6 (NSYNC); also elsewhere on the board
/SPI2_SCK: R400.1; also elsewhere on the board
GND: C400.2, C401.2, C402.2, C403.2, C404.2, C405.1, D400.1, J400.2 (Ext), R402.2, U400.3 (GND), U401.2 (V-); also elsewhere on the board
unnamed: C403.1, R401.1, R403.2
unnamed: C406.1, R403.1, R404.2

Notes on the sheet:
output voltage will range between 0V and 3.3V
DC offset (op-amp biasO)is generated by DAC
3rd order butterworth reconstruction (low pass filter) fc=25khz
DAC & anti ALIASING FILTER & BNC

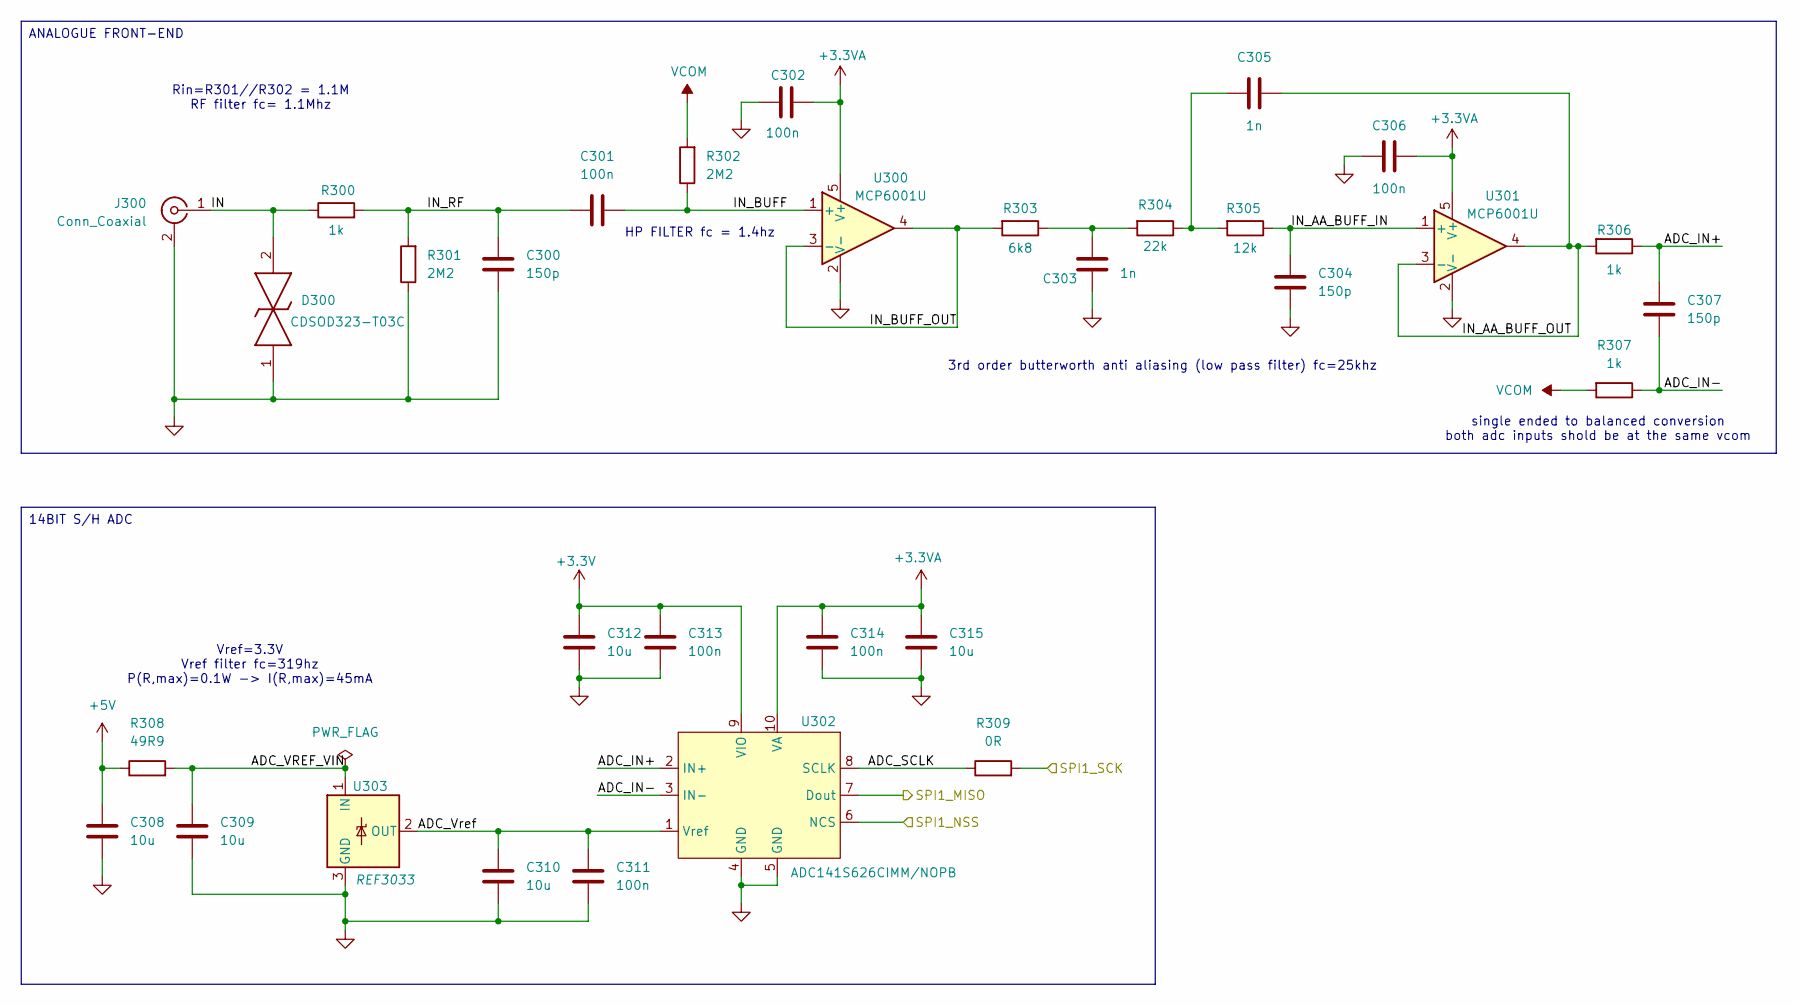
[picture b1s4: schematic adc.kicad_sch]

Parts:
C300, C304, C307: 150p; C_0402_1005Metric
C301, C302, C306, C311, C313, C314: 100n; C_0402_1005Metric
C303, C305: 1n; C_0402_1005Metric
C308, C309, C310, C312, C315: 10u; C_0603_1608Metric
D300: CDSOD323-T03C; SOD2513X114N; Mouser Part Number 652-CDSOD323-T03C
J300: Conn_Coaxial; BNC_Amphenol_B6252HB-NPP3G-50_Horizontal
R300, R306, R307: 1k; R_0402_1005Metric
R301, R302: 2M2; R_0402_1005Metric
R303: 6k8; R_0402_1005Metric
R304: 22k; R_0402_1005Metric
R305: 12k; R_0402_1005Metric
R308: 49R9; R_0402_1005Metric
R309: 0R; R_0402_1005Metric
U300, U301: MCP6001U; SOT-23-5
U302: ADC141S626CIMM/NOPB; SOIC-10-adc141s626
U303: REF3033; SOT-23

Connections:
+3.3V: C312.1, C313.1, U302.9 (VIO); also elsewhere on the board
+3.3VA: C302.2, C306.2, C314.1, C315.1, U300.5 (V+), U301.5 (V+), U302.10 (VA); also elsewhere on the board
+5V: C308.1, R308.1; also elsewhere on the board
/ADC/ADC_IN+: C307.1, R306.1, U302.2 (IN+)
/ADC/ADC_IN-: C307.2, R307.1, U302.3 (IN-)
/ADC/ADC_SCLK: R309.1, U302.8 (SCLK)
/ADC/ADC_VREF_VIN: C309.1, R308.2, U303.1 (IN)
/ADC/ADC_Vref: C310.1, C311.1, U302.1 (Vref), U303.2 (OUT)
/ADC/IN: D300.2, J300.1 (In), R300.1
/ADC/IN_AA_BUFF_IN: C304.1, R305.1, U301.1 (+)
/ADC/IN_AA_BUFF_OUT: C305.2, R306.2, U301.3 (-), U301.4
/ADC/IN_BUFF: C301.2, R302.1, U300.1 (+)
/ADC/IN_BUFF_OUT: R303.2, U300.3 (-), U300.4
/ADC/IN_RF: C300.1, C301.1, R300.2, R301.2
/SPI1_MISO: U302.7 (Dout); also elsewhere on the board
/SPI1_NSS: U302.6 (NCS); also elsewhere on the board
/SPI1_SCK: R309.2; also elsewhere on the board
GND: C300.2, C302.1, C303.2, C304.2, C306.1, C308.2, C309.2, C310.2, C311.2, C312.2, C313.2, C314.2, C315.2, D300.1, J300.2 (Ext), R301.1, U300.2 (V-), U301.2 (V-), U302.4 (GND), U302.5 (GND), U303.3 (GND); also elsewhere on the board
unnamed: C303.1, R303.1, R304.2
unnamed: C305.1, R304.1, R305.2
VCOM: R302.2, R307.2; also elsewhere on the board

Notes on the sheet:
Vref=3.3V Vref filter fc=319hz P(R,max)=0.1W -> I(R,max)=45mA
single ended to balanced conversion both adc inputs shold be at the same vcom
Rin=R301//R302 = 1.1M RF filter fc= 1.1Mhz
HP FILTER fc = 1.4hz
3rd order butterworth anti aliasing (low pass filter) fc=25khz
ANALOGUE FRONT-END
14BIT S/H ADC

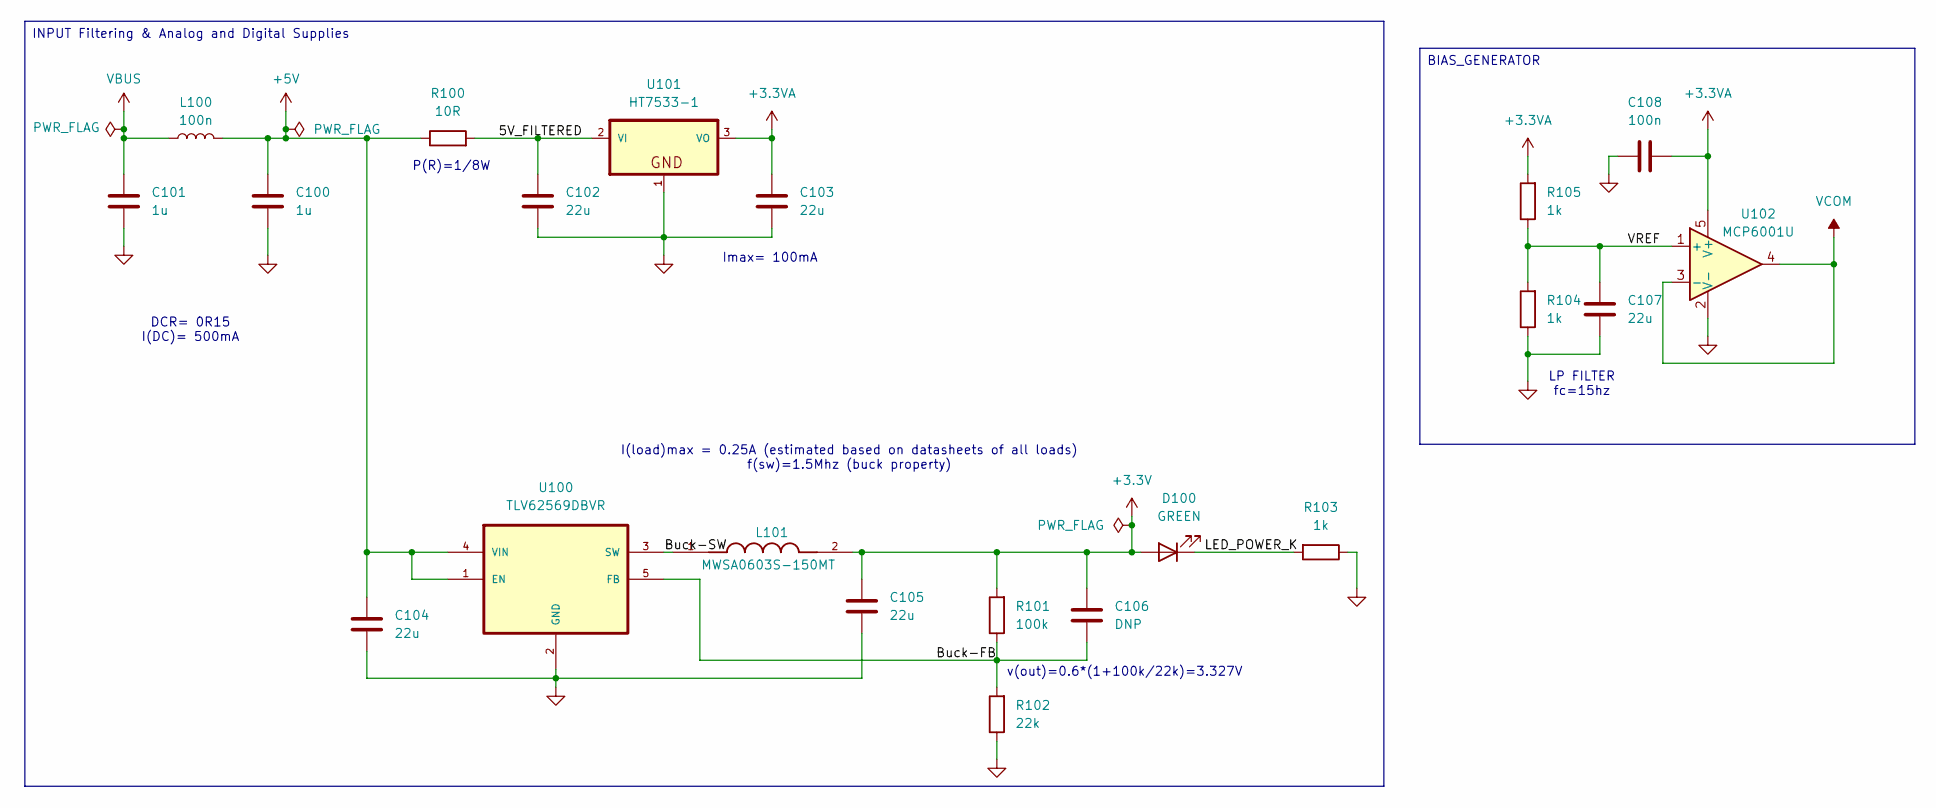
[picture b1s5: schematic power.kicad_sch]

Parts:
C100, C101: 1u; C_0603_1608Metric
C102, C103, C104, C105, C107: 22u; C_0805_2012Metric
C106: DNP; C_0402_1005Metric
C108: 100n; C_0402_1005Metric
D100: GREEN; LED_0603_1608Metric
L100: 100n; L_0402_1005Metric
L101: MWSA0603S-150MT; INDM7066X300N; PARTREV 2022/10/12
R100: 10R; R_0805_2012Metric
R101: 100k; R_0402_1005Metric
R102: 22k; R_0402_1005Metric
R103, R104, R105: 1k; R_0402_1005Metric
U100: TLV62569DBVR; TLV-SOT95P280X145-5N
U101: HT7533-1; LDO-SOT89
U102: MCP6001U; SOT-23-5

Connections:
+3.3V: C105.1, C106.1, D100.2 (A), L101.2, R101.2; also elsewhere on the board
+3.3VA: C103.1, C108.2, R105.2, U101.3 (VO), U102.5 (V+); also elsewhere on the board
+5V: C100.1, C104.1, L100.2, R100.1, U100.1 (EN), U100.4 (VIN); also elsewhere on the board
/Power/5V_FILTERED: C102.1, R100.2, U101.2 (VI), U101.2@1 (VI)
/Power/Buck-FB: C106.2, R101.1, R102.2, U100.5 (FB)
/Power/Buck-SW: L101.1, U100.3 (SW)
/Power/LED_POWER_K: D100.1 (K), R103.2
/Power/VREF: C107.1, R104.2, R105.1, U102.1 (+)
GND: C100.2, C101.2, C102.2, C103.2, C104.2, C105.2, C107.2, C108.1, R102.1, R103.1, R104.1, U100.2 (GND), U101.1, U102.2 (V-); also elsewhere on the board
VBUS: C101.1, L100.1; also elsewhere on the board
VCOM: U102.3 (-), U102.4; also elsewhere on the board

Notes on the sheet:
DCR= 0R15 I(DC)= 500mA
Imax= 100mA
v(out)=0.6*(1+100k/22k)=3.327V
LP FILTER fc=15hz
I(load)max = 0.25A (estimated based on datasheets of all loads) f(sw)=1.5Mhz (buck property)
P(R)=1/8W
INPUT Filtering & Analog and Digital Supplies
BIAS_GENERATOR

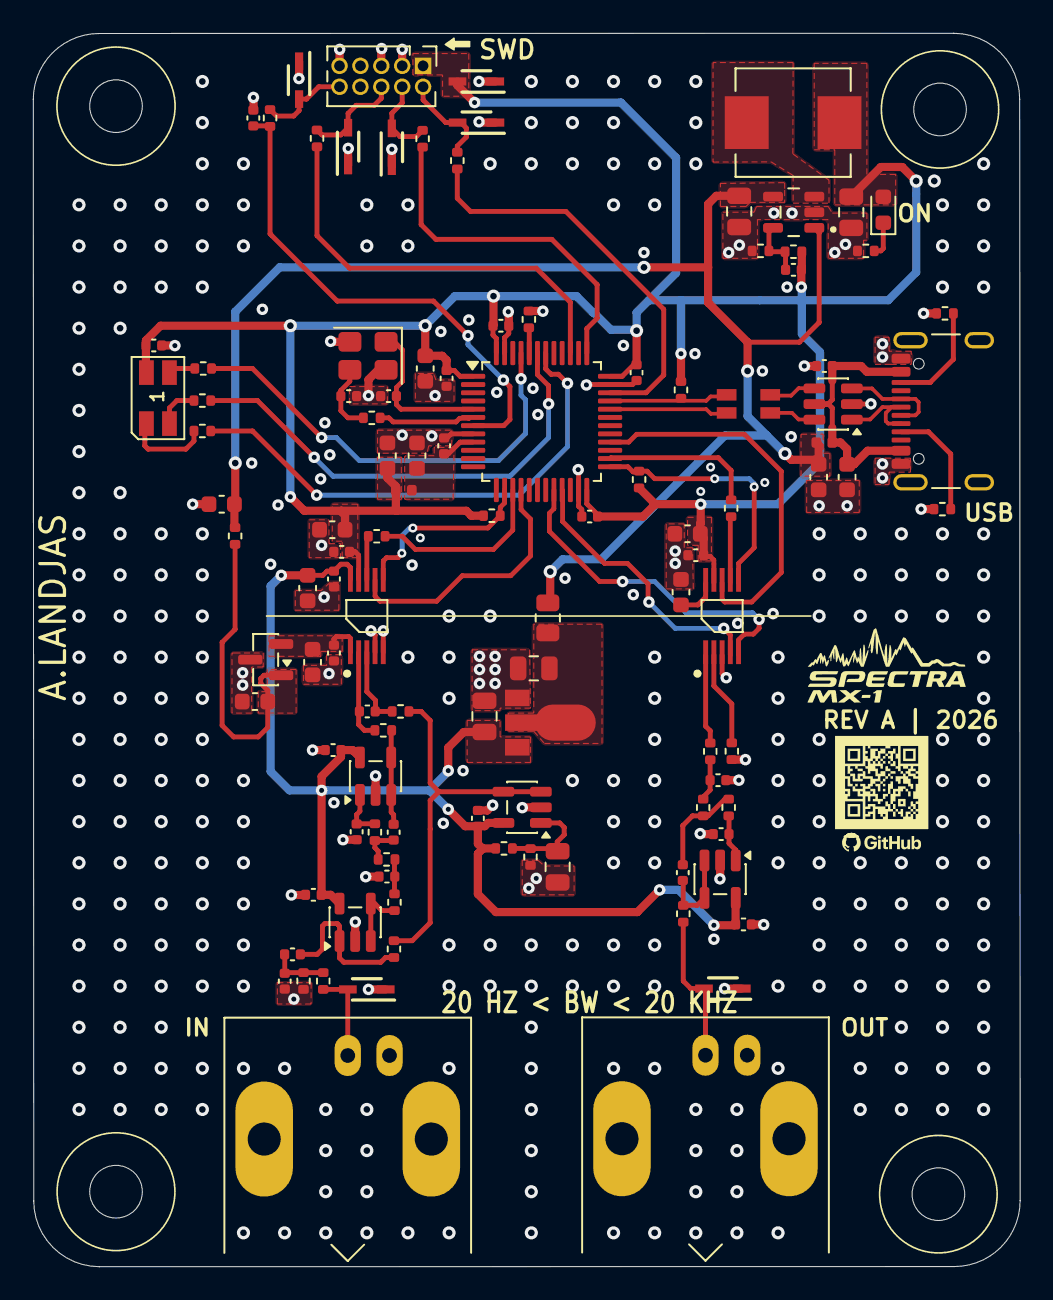
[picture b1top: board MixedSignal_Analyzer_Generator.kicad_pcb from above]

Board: 4 copper layers, 60.0 x 75.0 mm, 114 parts (0 on the bottom side), 68 nets.
